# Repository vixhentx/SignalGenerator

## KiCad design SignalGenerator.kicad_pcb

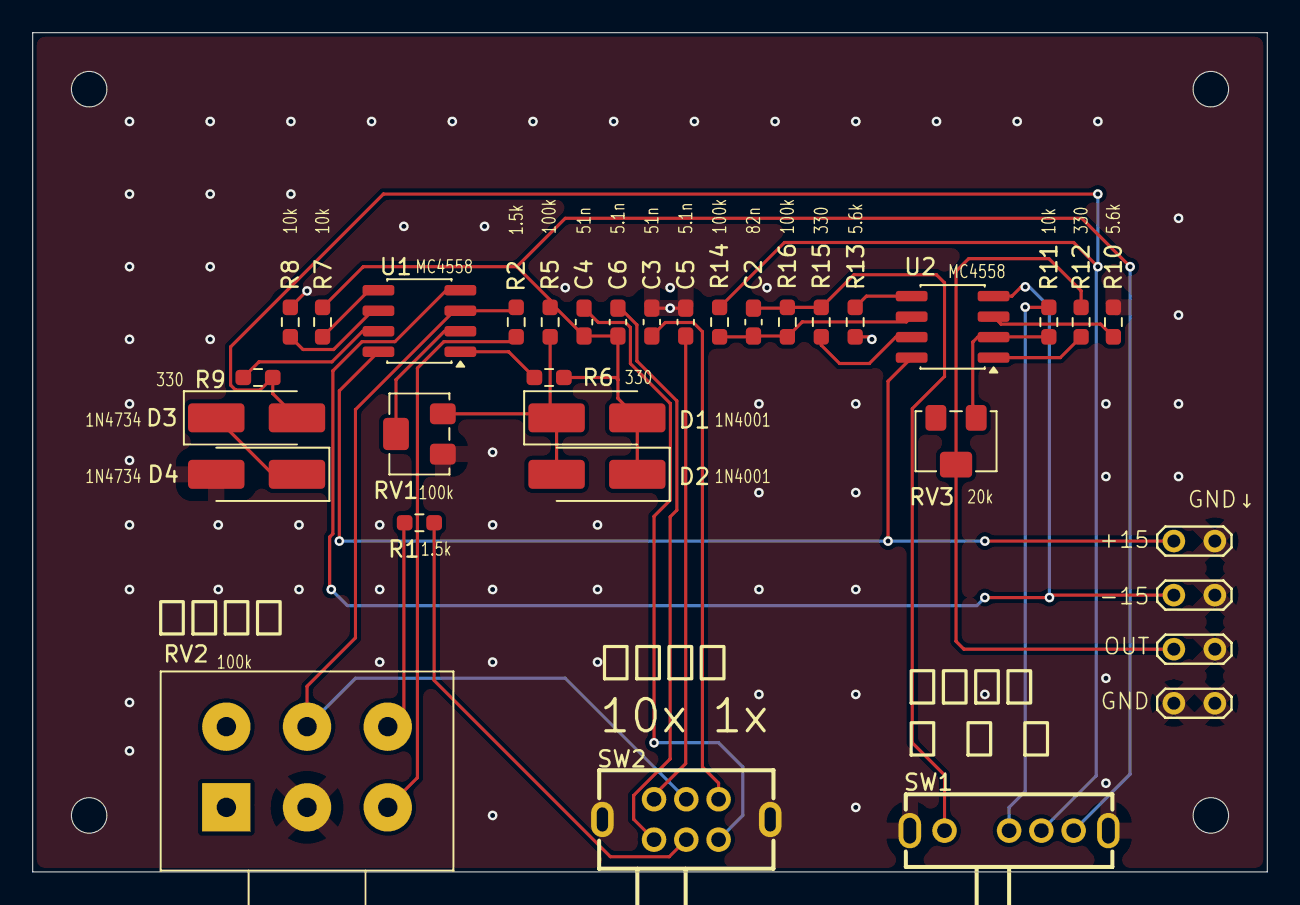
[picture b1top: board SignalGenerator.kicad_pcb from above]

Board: 2 copper layers, 76.5 x 52.0 mm, 34 parts (0 on the bottom side), 29 nets.

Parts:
C2: 82n; C_0603_1608Metric_Pad1.08x0.95mm_HandSolder
C3, C4: 51n; C_0603_1608Metric_Pad1.08x0.95mm_HandSolder
C5, C6: 5.1n; C_0603_1608Metric_Pad1.08x0.95mm_HandSolder
D1, D2: 1N4001; D_SMA_Handsoldering
D3, D4: 1N4734; D_SMA_Handsoldering
R1, R2: 1.5k; R_0603_1608Metric_Pad0.98x0.95mm_HandSolder
R5, R14, R16: 100k; R_0603_1608Metric_Pad0.98x0.95mm_HandSolder
R6, R9, R12, R15: 330; R_0603_1608Metric_Pad0.98x0.95mm_HandSolder
R7, R8, R11: 10k; R_0603_1608Metric_Pad0.98x0.95mm_HandSolder
R10, R13: 5.6k; R_0603_1608Metric_Pad0.98x0.95mm_HandSolder
RV1: 100k; Potentiometer_Bourns_3224W_Vertical
RV2: 100k; Potentiometer_Alps_RK163_Dual_Horizontal
RV3: 20k; Potentiometer_Bourns_3224W_Vertical
SW1: SK13D07VG4; SW-TH_SK13D07VG4
SW2: SK-22D02-L4; SW-TH_SK-22D02-L4
TP1, TP2, TP3, TP4: TestPoint_2Pole; TestPoint_2Pads_Pitch2.54mm_Drill0.8mm
U1, U2: MC4558; SOP-8_3.76x4.96mm_P1.27mm

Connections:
+15V: TP1.2, U1.8 (V+), U2.8 (V+)
-15V: TP2.2, U1.4 (V-), U2.4 (V-)
/Scaling/V_{i}: R11.1, SW1.3
/SinGenerator/CF1_A: R2.2, RV2.5, SW2.2, U1.3 (+)
/SinGenerator/CF2_A: R1.2, SW2.5
/V_{out}: R12.2, RV3.2, TP3.2
/V_{sin}: C4.2, C6.2, D1.2 (A), D2.1 (K), R5.2, R6.2, R7.1, SW1.5
/V_{square}: D3.2 (A), R9.2, R14.1, SW1.4
/V_{tri}: C2.2, R15.2, R16.2, SW1.1
GND: C3.2, C5.2, D4.2 (A), R8.1, R10.1, R13.1, RV1.1, RV2.2, SW1.6, SW1.7, SW2.7, SW2.8, TP1.1, TP2.1, TP3.1, TP4.1, TP4.2
unnamed: C3.1, SW2.3
unnamed: C4.1, SW2.6
unnamed: C5.1, SW2.1
unnamed: C6.1, SW2.4
unnamed: D1.1 (K), D2.2 (A), R5.1, RV1.3
unnamed: D3.1 (K), D4.1 (K)
unnamed: R1.1, RV2.6
unnamed: R2.1, RV2.3
unnamed: R6.1, U1.1
unnamed: R9.1, U1.7
unnamed: R12.1, U2.1
unnamed: R15.1, U2.7
unnamed: RV1.2, U1.2 (-)
unnamed: R7.2, U1.5 (+)
unnamed: R8.2, U1.6 (-)
unnamed: R10.2, U2.3 (+)
unnamed: R11.2, RV3.1, U2.2 (-)
unnamed: R13.2, U2.5 (+)
unnamed: C2.1, R14.2, R16.1, U2.6 (-)
